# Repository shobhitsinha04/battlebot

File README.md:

# Battlebot

A 2 lb antweight combat robot built for ECE 445 (Senior Design) at the University of Illinois Urbana-Champaign, Spring 2026. It runs on a custom ESP32 control PCB, drives two wheels plus a brushless spinning weapon, and is controlled wirelessly from an Xbox controller.

## Results

| Requirement | Target | Measured |
| --- | --- | --- |
| End-to-end wireless latency | under 100 ms | 75 ms |
| Command update rate | stable | 50 Hz |
| Wireless range | 15 ft line of sight | stable at 15 ft |
| Motor shutdown on signal loss | within 250 ms | within 250 ms (firmware watchdog) |
| Weight class | 2 lb antweight | met |

## System overview

- **Control** ESP32 firmware receives drive and weapon commands over BLE. A Python host script maps Xbox controller input to left/right motor PWM with deadzone, inversion and range limiting.
- **Power** 4S LiPo feeding a protected power path (switch, TVS diode) and a buck converter to a stable 3.3 V logic rail.
- **Actuation** Two brushed drive motors on the custom board. The brushless weapon was first driven with a TI MCF8316A and later moved to an external ESC using servo-style PWM for reliability.
- **Safety** A 250 ms command watchdog stops every motor if the controller link drops.
- **Mechanical** 3D-printed PLA chassis with bolt-on skids, wheel protectors, and brushless weapon motor arms, iterated through several print and fit cycles.

## Hardware

The PCB was designed in KiCad. Open `hardware/battlebot.kicad_pro` to view the schematic and layout.

## Mechanical design

The chassis is a low, wide box with defined internal zones for the battery, PCB, drive motors and wiring, so the electrical team could integrate without redesigning the shell. Skids, wheel protectors and weapon arms are separate bolt-on parts so each could be revised and reprinted on its own. A failed weapon shaft coupler in April led to a redesigned wheel-to-shaft mount and brushless-specific motor arms.

## Repository layout

```
assets/      Photos used in this README
hardware/    KiCad schematic, PCB layout, custom symbols and footprints
notebook/    Engineering lab notebooks for each team member, with build photos
```

## Team

| Member | Focus |
| --- | --- |
| Abhinav Garg | Firmware, controller interface, motor control, system verification |
| Rahul Krishnamoorthy | PCB, power path, protection, electrical testing |
| Shobhit Sinha | Chassis, motor mounts, skids, wheels, weapon mounting, printed-part design |

Full dated engineering notes live in [`notebook/notebooks`](notebook/notebooks). Original repositories by Abhinav Garg are at [ece445-pcb](https://github.com/AbhinavGarg90/ece445-pcb) and [ece445-lab-notebook](https://github.com/AbhinavGarg90/ece445-lab-notebook).

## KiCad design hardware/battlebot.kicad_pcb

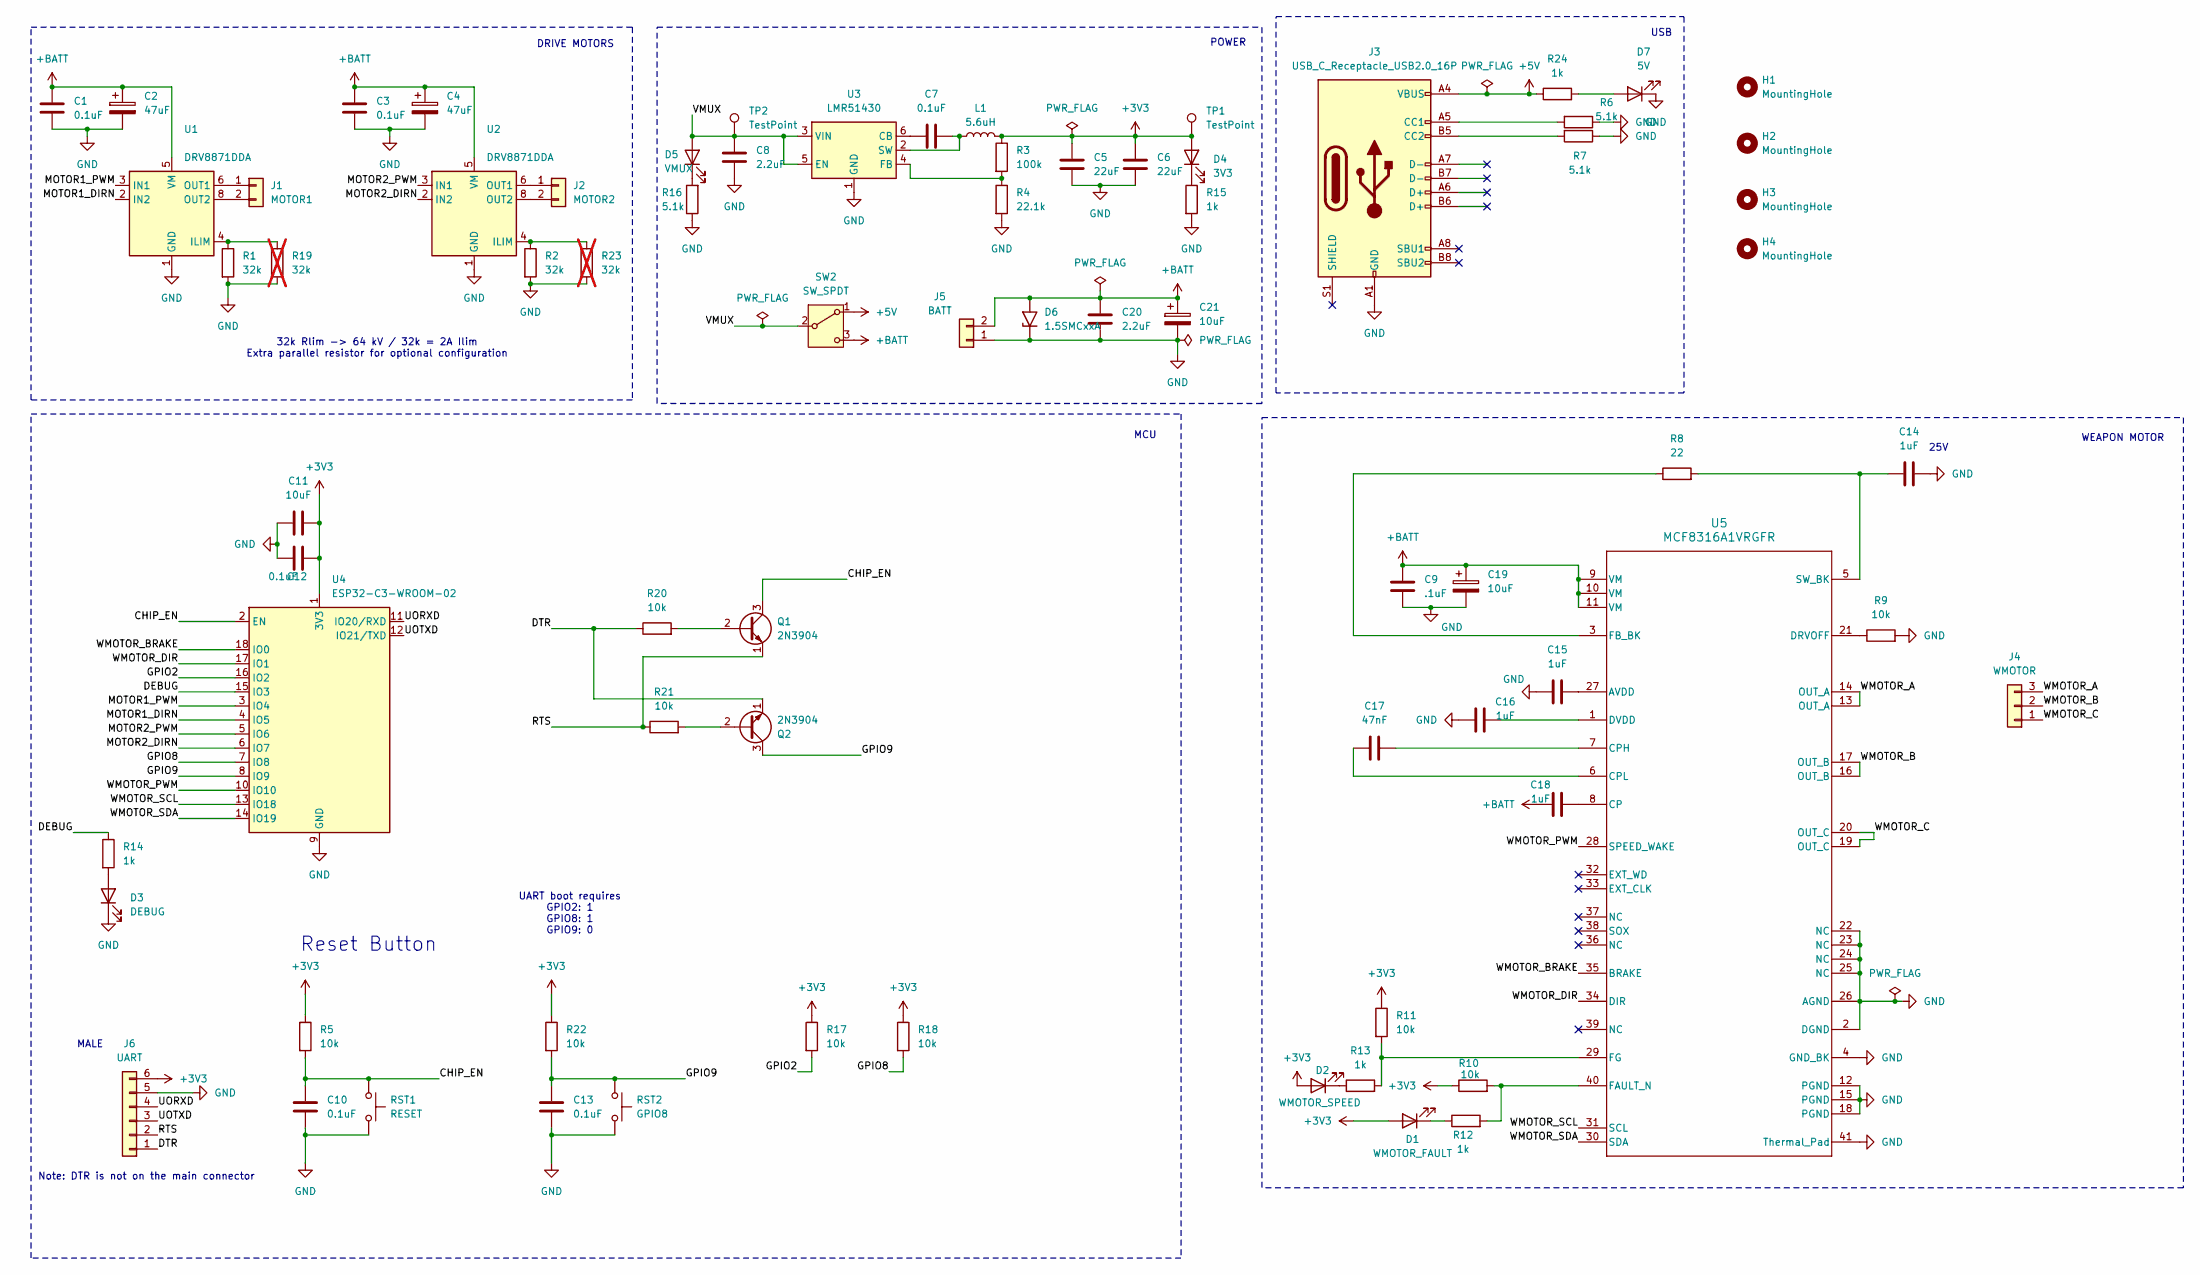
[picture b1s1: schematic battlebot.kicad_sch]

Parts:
C1, C3, C7, C10, C12, C13: 0.1uF; C_0805_2012Metric
C2, C4: 47uF; CP_Radial_D8.0mm_P5.00mm
C5, C6: 22uF; C_0805_2012Metric
C8, C20: 2.2uF; C_0805_2012Metric
C9: .1uF; C_0805_2012Metric
C11: 10uF; C_0805_2012Metric
C14, C15, C16, C18: 1uF; C_0805_2012Metric
C17: 47nF; C_0805_2012Metric
C19, C21: 10uF; CP_Radial_D8.0mm_P5.00mm
D1: WMOTOR_FAULT; C_0805_2012Metric
D2: WMOTOR_SPEED; C_0805_2012Metric
D3: DEBUG; C_0805_2012Metric
D4: 3V3; C_0805_2012Metric
D5: VMUX; C_0805_2012Metric
D6: 1.5SMCxxA; D_SMC
D7: 5V; C_0805_2012Metric
H1, H2, H3, H4: MountingHole; MountingHole_2.2mm_M2
J1: MOTOR1; PinSocket_1x02_P2.54mm_Vertical
J2: MOTOR2; PinSocket_1x02_P2.54mm_Vertical
J3: USB_C_Receptacle_USB2.0_16P; USB_C_Receptacle_G-Switch_GT-USB-7010ASV
J4: WMOTOR; PinHeader_1x03_P2.54mm_Vertical
J5: BATT; PinHeader_1x02_P2.54mm_Vertical
J6: UART; PinHeader_1x06_P2.54mm_Vertical
L1: 5.6uH; L_0805_2012Metric
Q1, Q2: 2N3904; TO-92_Inline
R1, R2: 32k; R_0805_2012Metric
R3: 100k; R_0805_2012Metric
R4: 22.1k; R_0805_2012Metric
R5, R9, R10, R11, R17, R18, R20, R21, R22: 10k; R_0805_2012Metric
R6, R7, R16: 5.1k; R_0805_2012Metric
R8: 22; R_0805_2012Metric
R12, R13, R14, R15, R24: 1k; R_0805_2012Metric
R19, R23: 32k; R_0805_2012Metric; not fitted
RST1: RESET; SW_TH_Tactile_Omron_B3F-100x
RST2: GPIO8; SW_TH_Tactile_Omron_B3F-100x
SW2: SW_SPDT; SW_SPDT_CK_JS102011SAQN
TP1, TP2: TestPoint
U1, U2: DRV8871DDA; Texas_HTSOP-8-1EP_3.9x4.9mm_P1.27mm_EP2.95x4.9mm_Mask2.4x3.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
U3: LMR51430; SOT-23-6
U4: ESP32-C3-WROOM-02; ESP32-C3-WROOM-02U
U5: MCF8316A1VRGFR; RGF0040E-IPC_A

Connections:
+3V3: C5.1, C6.1, C11.1, C12.1, D1.2 (A), D2.2 (A), D4.2 (A), J6.6, L1.2, R3.1, R5.1, R10.1, R11.1, R17.1, R18.1, R22.1, TP1.1, U4.1 (3V3)
+5V: J3.A4 (VBUS), J3.A9 (VBUS), J3.B4 (VBUS), J3.B9 (VBUS), R24.1, SW2.1 (A)
+BATT: C1.1, C2.1, C3.1, C4.1, C9.1, C18.1, C19.1, C20.1, C21.1, D6.2 (A2), J5.2, SW2.3 (C), U1.5 (VM), U2.5 (VM), U5.9 (VM), U5.10 (VM), U5.11 (VM)
/CHIP_EN: C10.1, Q1.3 (C), R5.2, RST1.1, U4.2 (EN)
/DEBUG: R14.1, U4.15 (IO3)
/DTR: J6.1, Q2.1 (E), R20.1
/GPIO2: R17.2, U4.16 (IO2)
/GPIO8: R18.2, U4.7 (IO8)
/GPIO9: C13.1, Q2.3 (C), R22.2, RST2.1, U4.8 (IO9)
/MOTOR1_DIRN: U1.2 (IN2), U4.4 (IO5)
/MOTOR1_PWM: U1.3 (IN1), U4.3 (IO4)
/MOTOR2_DIRN: U2.2 (IN2), U4.6 (IO7)
/MOTOR2_PWM: U2.3 (IN1), U4.5 (IO6)
/RTS: J6.2, Q1.1 (E), R21.1
/UORXD: J6.4, U4.11 (IO20/RXD)
/UOTXD: J6.3, U4.12 (IO21/TXD)
/VMUX: C8.1, D5.2 (A), SW2.2 (B), TP2.1, U3.3 (VIN), U3.5 (EN)
/WMOTOR_A: J4.3, U5.13 (OUT_A), U5.14 (OUT_A)
/WMOTOR_B: J4.2, U5.16 (OUT_B), U5.17 (OUT_B)
/WMOTOR_BRAKE: U4.18 (IO0), U5.35 (BRAKE)
/WMOTOR_C: J4.1, U5.19 (OUT_C), U5.20 (OUT_C)
/WMOTOR_DIR: U4.17 (IO1), U5.34 (DIR)
/WMOTOR_PWM: U4.10 (IO10), U5.28 (SPEED_WAKE)
/WMOTOR_SCL: U4.13 (IO18), U5.31 (SCL)
/WMOTOR_SDA: U4.14 (IO19), U5.30 (SDA)
GND: C1.2, C2.2, C3.2, C4.2, C5.2, C6.2, C8.2, C9.2, C10.2, C11.2, C12.2, C13.2, C14.2, C15.1, C16.1, C19.2, C20.2, C21.2, D3.1 (K), D6.1 (A1), D7.1 (K), J3.A1 (GND), J3.A12 (GND), J3.B1 (GND), J3.B12 (GND), J5.1, J6.5, R1.2, R2.2, R4.2, R6.1, R7.1, R9.2, R15.2, R16.1, R19.2, R23.2, RST1.2, RST2.2, U1.1 (GND), U1.7 (GND), U1.9 (GND), U2.1 (GND), U2.7 (GND), U2.9 (GND), U3.1 (GND), U4.9 (GND), U4.19 (GND), U5.2 (DGND), U5.4 (GND_BK), U5.12 (PGND), U5.15 (PGND), U5.18 (PGND), U5.22 (NC), U5.23 (NC), U5.24 (NC), U5.25 (NC), U5.26 (AGND), U5.41 (Thermal_Pad)
unnamed: D1.1 (K), R12.1
unnamed: D2.1 (K), R13.1
unnamed: D3.2 (A), R14.2
unnamed: D4.1 (K), R15.1
unnamed: D5.1 (K), R16.2
unnamed: D7.2 (A), R24.2
unnamed: J1.1, U1.6 (OUT1)
unnamed: J1.2, U1.8 (OUT2)
unnamed: J2.1, U2.6 (OUT1)
unnamed: J2.2, U2.8 (OUT2)
unnamed: J3.A5 (CC1), R6.2
unnamed: J3.B5 (CC2), R7.2
unnamed: Q1.2 (B), R20.2
unnamed: Q2.2 (B), R21.2
unnamed: R1.1, R19.1, U1.4 (ILIM)
unnamed: R2.1, R23.1, U2.4 (ILIM)
unnamed: C7.2, U3.6 (CB)
unnamed: R3.2, R4.1, U3.4 (FB)
unnamed: C7.1, L1.1, U3.2 (SW)
unnamed: C15.2, U5.27 (AVDD)
unnamed: C18.2, U5.8 (CP)
unnamed: C17.2, U5.7 (CPH)
unnamed: C17.1, U5.6 (CPL)
unnamed: R9.1, U5.21 (DRVOFF)
unnamed: C16.2, U5.1 (DVDD)
unnamed: R10.2, R12.2, U5.40 (FAULT_N)
unnamed: R8.1, U5.3 (FB_BK)
unnamed: R11.2, R13.2, U5.29 (FG)
unnamed: C14.1, R8.2, U5.5 (SW_BK)

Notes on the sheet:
MALE
WEAPON MOTOR
Reset Button
POWER
USB
UART boot requires GPIO2: 1 GPIO8: 1 GPIO9: 0
DRIVE MOTORS
25V
MCU
32k Rlim -> 64 kV / 32k = 2A Ilim Extra parallel resistor for optional configuration
Note: DTR is not on the main connector

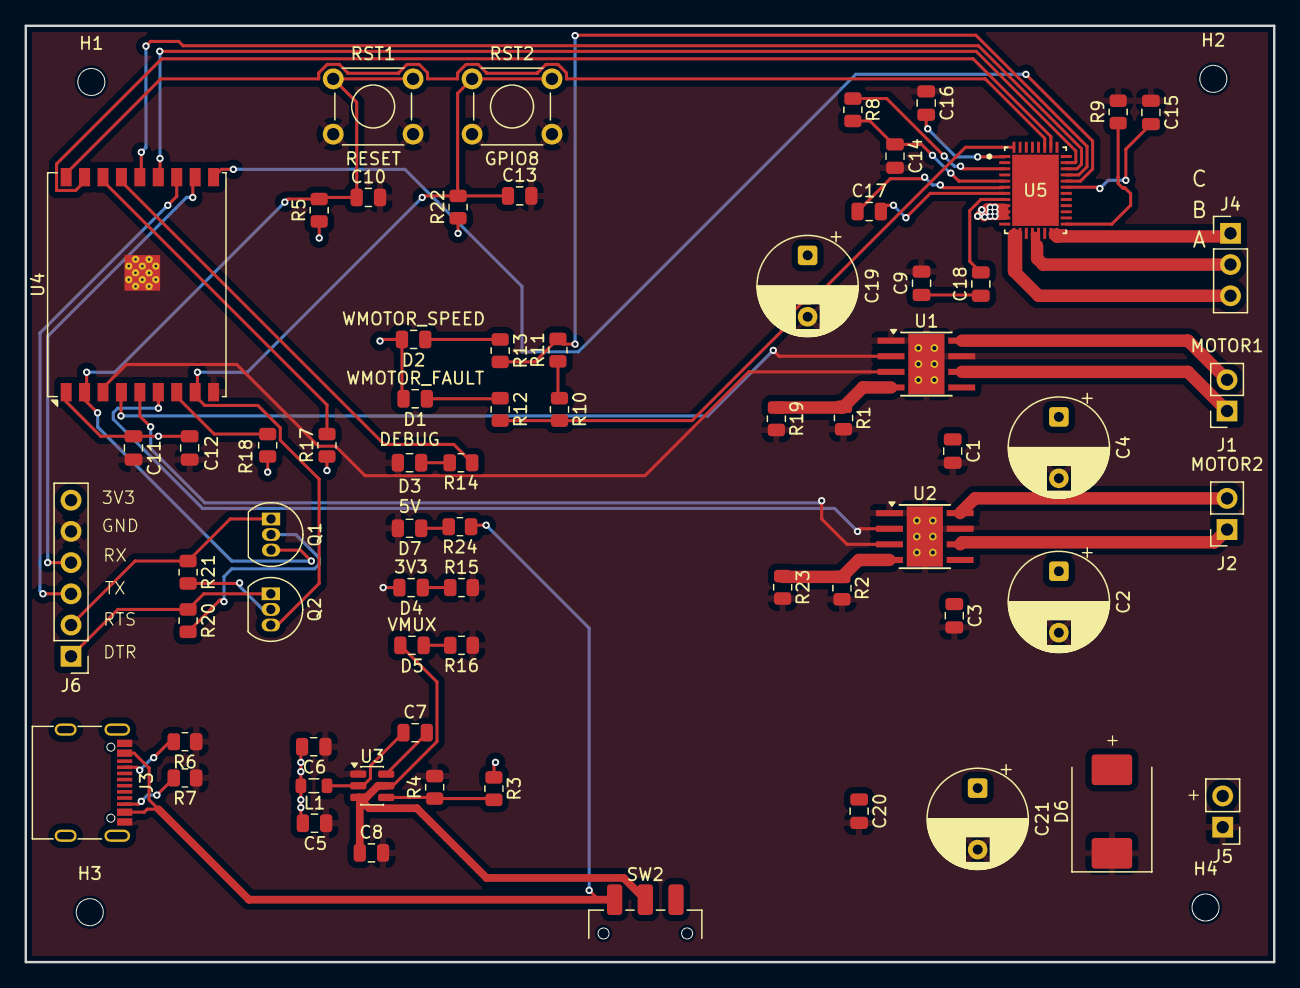
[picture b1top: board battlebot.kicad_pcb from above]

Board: 2 copper layers, 101.6 x 76.2 mm, 73 parts (0 on the bottom side), 55 nets.
